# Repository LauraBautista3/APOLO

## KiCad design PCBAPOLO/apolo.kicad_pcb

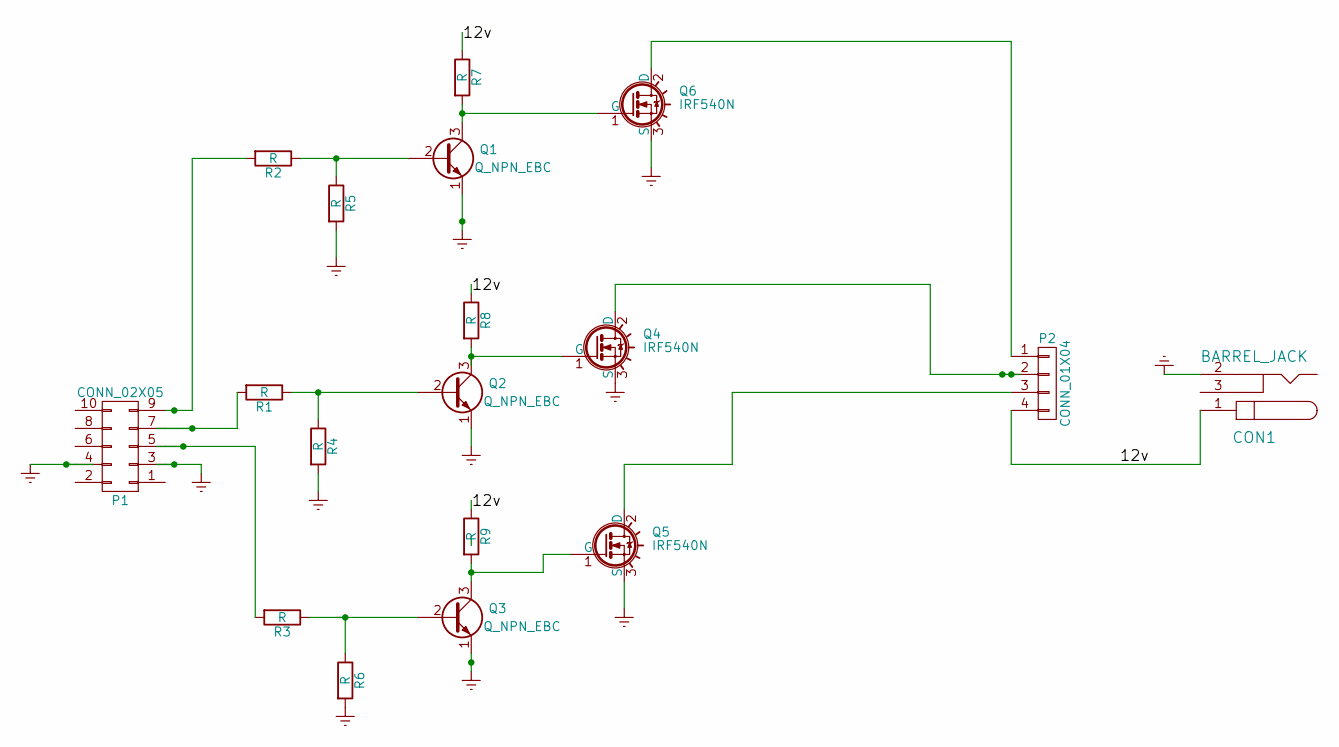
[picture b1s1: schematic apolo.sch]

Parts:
CON1: BARREL_JACK; JACK_ALIM
P1: CONN_02X05
P2: CONN_01X04
Q1, Q2, Q3: Q_NPN_EBC
Q4, Q5, Q6: IRF540N
R1, R2, R3, R4, R5, R6, R7, R8, R9: R; Resistor_Horizontal_RM15mm

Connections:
/12v: CON1.1, P2.4, R7.1, R8.1, R9.1
Earth: CON1.2, P1.3, P1.4, Q1.1 (E), Q2.1 (E), Q3.1 (E), Q4.3 (S), Q5.3 (S), Q6.3 (S), R4.2, R5.2, R6.2
unnamed: P1.5, R3.2
unnamed: P1.7, R1.2
unnamed: P1.9, R2.2
unnamed: P2.1, Q6.2 (D)
unnamed: P2.2, Q4.2 (D)
unnamed: P2.3, Q5.2 (D)
unnamed: Q1.2 (B), R2.1, R5.1
unnamed: Q1.3 (C), Q6.1 (G), R7.2
unnamed: Q2.2 (B), R1.1, R4.1
unnamed: Q2.3 (C), Q4.1 (G), R8.2
unnamed: Q3.2 (B), R3.1, R6.1
unnamed: Q3.3 (C), Q5.1 (G), R9.2

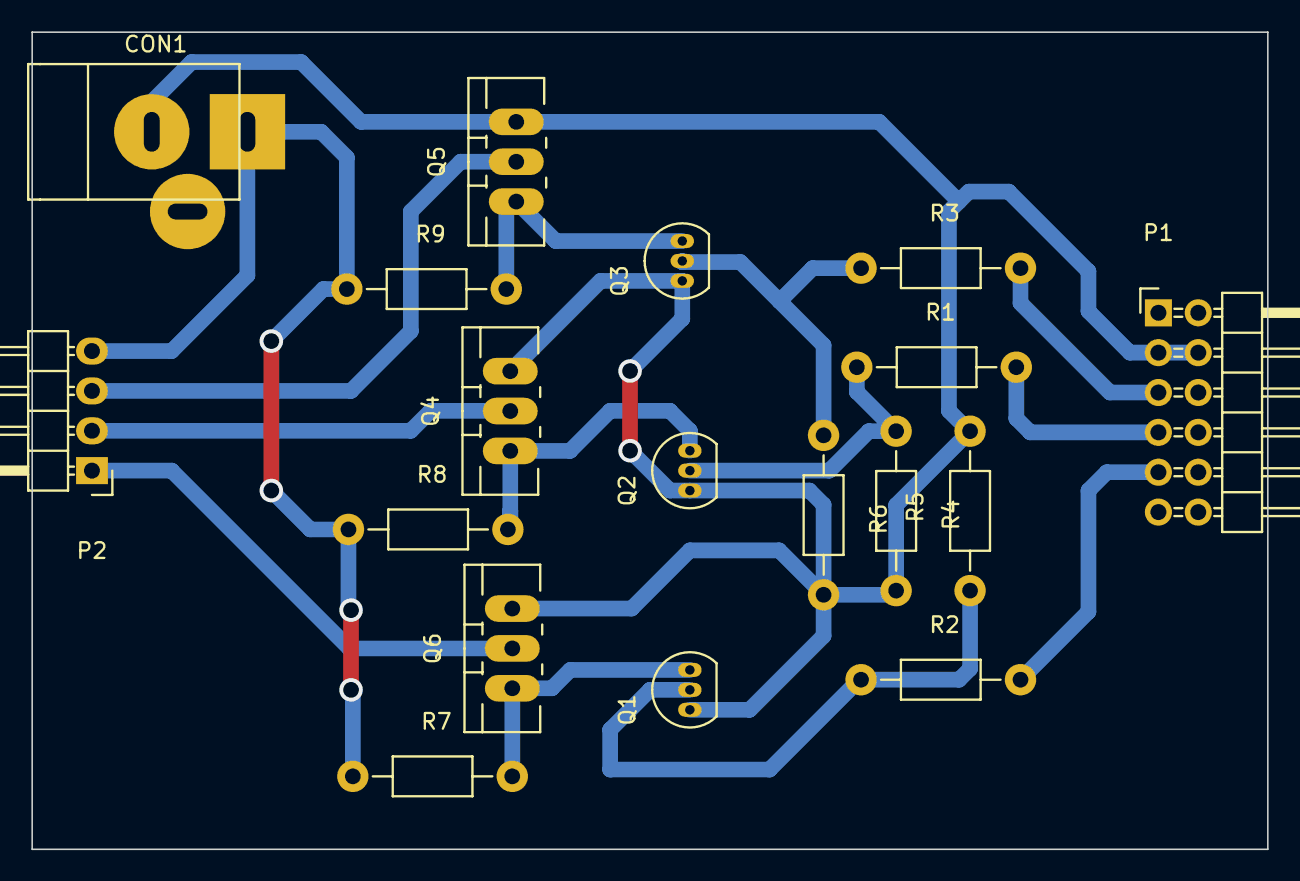
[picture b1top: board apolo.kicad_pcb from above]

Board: 2 copper layers, 78.7 x 52.1 mm, 18 parts (0 on the bottom side), 14 nets.

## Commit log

2015-10-02 prueba
2015-10-19 eee:
2015-10-19 ffefef
2015-10-20 fer2
2015-10-26 ignore2
2015-10-26 cambio uart
2015-10-27 GPIO_sirve
2015-10-27 "gpio okey"
2015-10-27 ok sleep example
2015-10-28 timer
2015-10-28 timer_dmx
2015-10-29 mdmx
2015-10-29 fer3
2015-10-29 uart_tx_dmx
2015-10-30 tx_dmx
2015-10-30 dmx_tiempo
2015-10-31 eclipse
2015-10-31 tiempo_dmx
2015-10-31 dmx-tiempo
2015-11-03 RX_dmx_fin
2015-11-03 rx_dmx
2015-11-04 dmxtxrx
2015-11-04 ultimo
2015-11-04 rxdmx
2015-11-09 dmxrxtx
2015-11-18 txrx
2015-11-18 rxtx
2015-11-25 pwm_provisional
2015-11-26 interrupciones_temprales
2015-11-27 interrupciones
2015-11-28 TX_funcionando
2015-12-01 rxtxdmx
2015-12-08 tx y rx funcionando sin pwm
2015-12-08 Diseños PCB APOLO
2015-12-09 rx y tx sin pwm
2015-12-09 Envio de datos por processing
2015-12-09 processing
2015-12-09 rx y tx
2015-12-10 porcessing
2015-12-12 periferico pwm
